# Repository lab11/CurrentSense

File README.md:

CurrentSense
============

CurrentSense is a tool for measuring current in embedded systems.

Usage
-----

Description of the inputs:

- **Power Supply**: 3.3-6 volts that supplies power to the measurement circuitry.
- **Optional Test Input**: This input can be used to power the load under test.
This is particularly useful for energy-harvesting or other systems where the input
power is not stable.
- **I_Sense**: The measurable output signal that is proportional to current.
To calculate current, divide the I_Sense signal (in volts) by the number
that corresponds to the selected range value. This will return the current
in amps.
- **Range**: Select the maximum current you want to measure. Select this as
close to the maximum you wish to measure as possible.
- **Load VCC Select**: This selects how you would like to power the load under
test. The options
  - Power Supply: Use the input from the power supply that is powering the
  measurement circuitry to also power the load.
  - 3V3: Use the onboard regulated 3.3 V rail to power the load.
  - Test Input: Use the external test input to power the load.
- **To Load**: Connect to VCC or the signal you wish to measure.
- **GND**: A set of ground pins for convenience.

Errata
------

The 300 mA range doesn't seem to work on v3.

----

V2 Notes
--------

You need a power selection jumper. You usually want to power the board externally,
in which case you'll want the jumper in the high position as pictured.

 - Connect external power (3.3-6V) to the EXT header at the top right.
   I usually also connect the external power to the GND header up here.
 - Connect the power supply for your target to VIN header.
 - Connect the VCC of your target to the VCC header
 - Connect the GND of your target to the GND header.
   I usually connect target GND to the GND header at the bottom, whose label is
   occluded by the screw.
 - Hook the scope probe to the test point at the top left (and GND anywhere)
 
The rest of the board is the same idea as above. Choose a range, measure voltage,
divide by the number on the board, get amperage.

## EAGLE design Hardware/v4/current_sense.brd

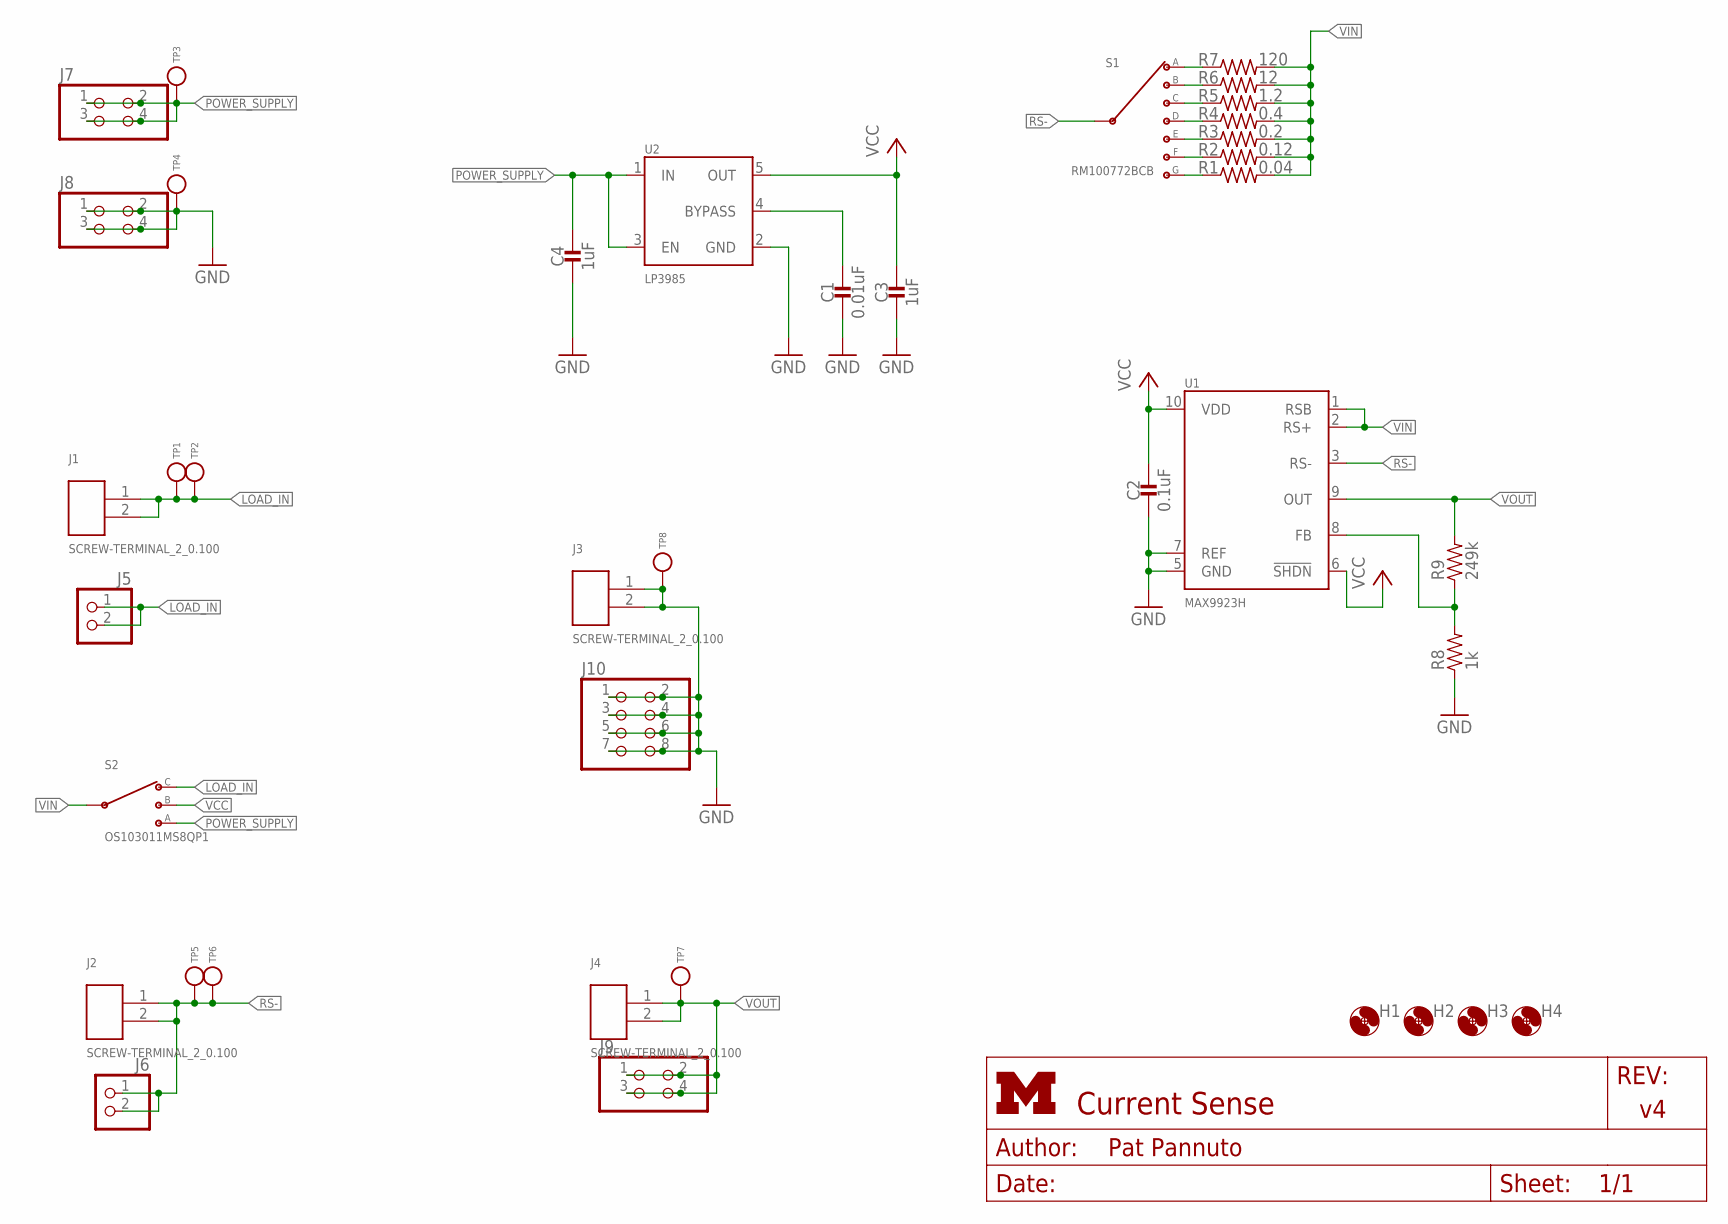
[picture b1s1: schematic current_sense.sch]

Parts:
C1: 0.01uF; 0603_CAP; MPN C1608X7R1E103K080AA; DIGIKEY 445-5100-1-ND
C2: 0.1uF; 0603_CAP; MPN C1608X7R1E104K080AA; DIGIKEY 445-1316-1-ND
C3, C4: 1uF; 0603_CAP; MPN C1608X7R1C105K080AC; DIGIKEY 445-1604-1-ND
H1, H2, H3, H4: MOUNT-HOLE3.2; 3,2
J1, J2, J3, J4: SCREW-TERMINAL_2_0.100; CONN_BLOCK_2
J5, J6: PINHD-1X2; 1X02
J7, J8, J9: PINHD-2X2; 2X02
J10: PINHD-2X4; 2X04
R1: 0.04; R1206; MPN RL1206FR-070R04L; DIGIKEY 311-.04LWCT-ND
R2: 0.12; R1206; MPN RL1632R-R120-F; DIGIKEY RL16R.12FCT-ND
R3: 0.2; R1206; MPN CSR1206FKR200; DIGIKEY CSR1206FKR200CT-ND
R4: 0.4; R1206; MPN RL1206FR-070R4L; DIGIKEY 311-.4LWCT-ND
R5: 1.2; R0805; MPN RL1220S-1R2-F; DIGIKEY RL12S1.2FCT-ND
R6: 12; R0805; MPN CPF0805B12RE1; DIGIKEY A103150CT-ND
R7: 120; R0805; MPN RG2012N-121-W-T1; DIGIKEY RG20N120WCT-ND
R8: 1k; 0603-RES; MPN ERA-3AEB102V; DIGIKEY P1.0KDBCT-ND
R9: 249k; 0603-RES; MPN ERA-3AEB2493V; DIGIKEY P249KDBCT-ND
S1: RM100772BCB; RM-SWITCH; MPN RM107772BCB; DIGIKEY CKN10705-ND
S2: OS103011MS8QP1; OS102011MS8QP1
TP1, TP2, TP3, TP4, TP5, TP6, TP7: TEST_POINT_0.040IN; TESTPOINT_0.040IN
TP8: TEST_POINT_0.112IN; TESTPOINT_0.112IN
U1: MAX9923H; UMAX10; MPN MAX9922EUB+T; DIGIKEY MAX9922EUB+TCT-ND
U2: LP3985; R-PDSO-G5

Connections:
GND: C1.2, C2.2, C3.2, C4.2, J3.1, J3.2, J8.1, J8.2, J8.3, J8.4, J10.1, J10.2, J10.3, J10.4, J10.5, J10.6, J10.7, J10.8, R8.1, TP4.TESTPOINT, TP8.1, U1.5 (GND), U1.7 (REF), U2.2 (GND)
LDO_BYPASS: C1.1, U2.4 (BYPASS)
LOAD_IN: J1.1, J1.2, J5.1, J5.2, S2.4 (3), TP1.TESTPOINT, TP2.TESTPOINT
POWER_SUPPLY: C4.1, J7.1, J7.2, J7.3, J7.4, S2.1, TP3.TESTPOINT, U2.1 (IN), U2.3 (EN)
RS-: J2.1, J2.2, J6.1, J6.2, S1.C (INPUT), TP5.TESTPOINT, TP6.TESTPOINT, U1.3 (RS-)
RS-_1MA: R6.1, S1.2 (B)
RS-_10MA: R5.1, S1.3 (C)
RS-_30MA: R4.1, S1.4 (D)
RS-_60MA: R3.1, S1.5 (E)
RS-_100MA: R2.1, S1.6 (F)
RS-_100UA: R7.1, S1.1 (A)
RS-_300MA: R1.1, S1.7 (G)
SENSE_FB: R8.2, R9.1, U1.8 (FB)
VCC: C2.1, C3.1, S2.3 (2), U1.6 (!SHDN), U1.10 (VDD), U2.5 (OUT)
VIN: R1.2, R2.2, R3.2, R4.2, R5.2, R6.2, R7.2, S2.2 (C), U1.1 (RSB), U1.2 (RS+)
VOUT: J4.1, J4.2, J9.1, J9.2, J9.3, J9.4, R9.2, TP7.TESTPOINT, U1.9 (OUT)

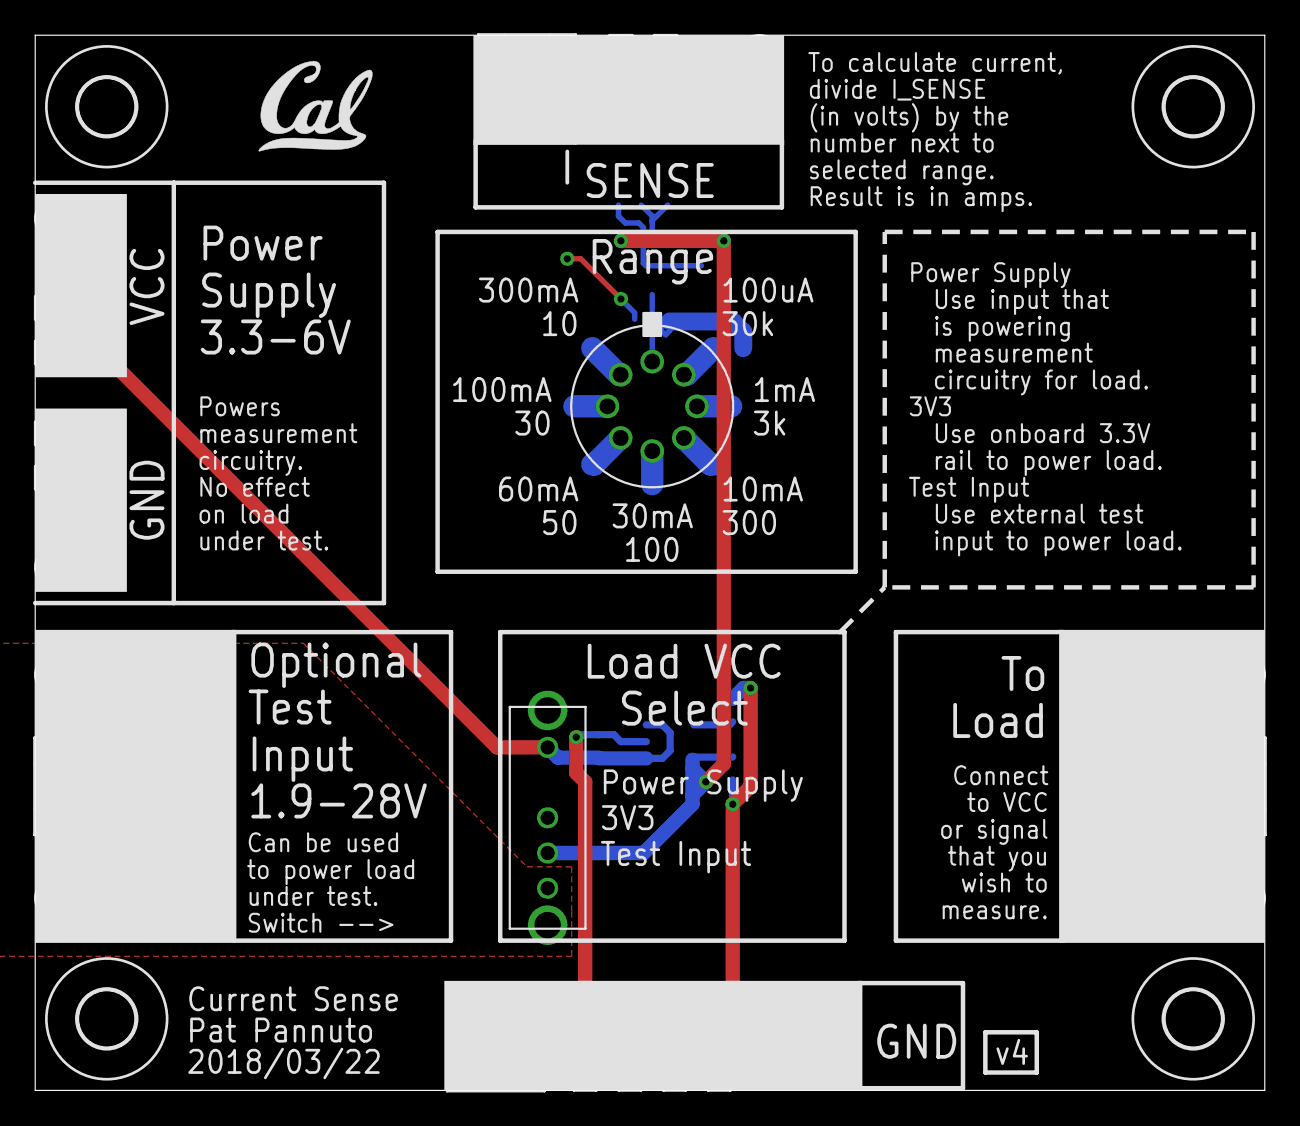
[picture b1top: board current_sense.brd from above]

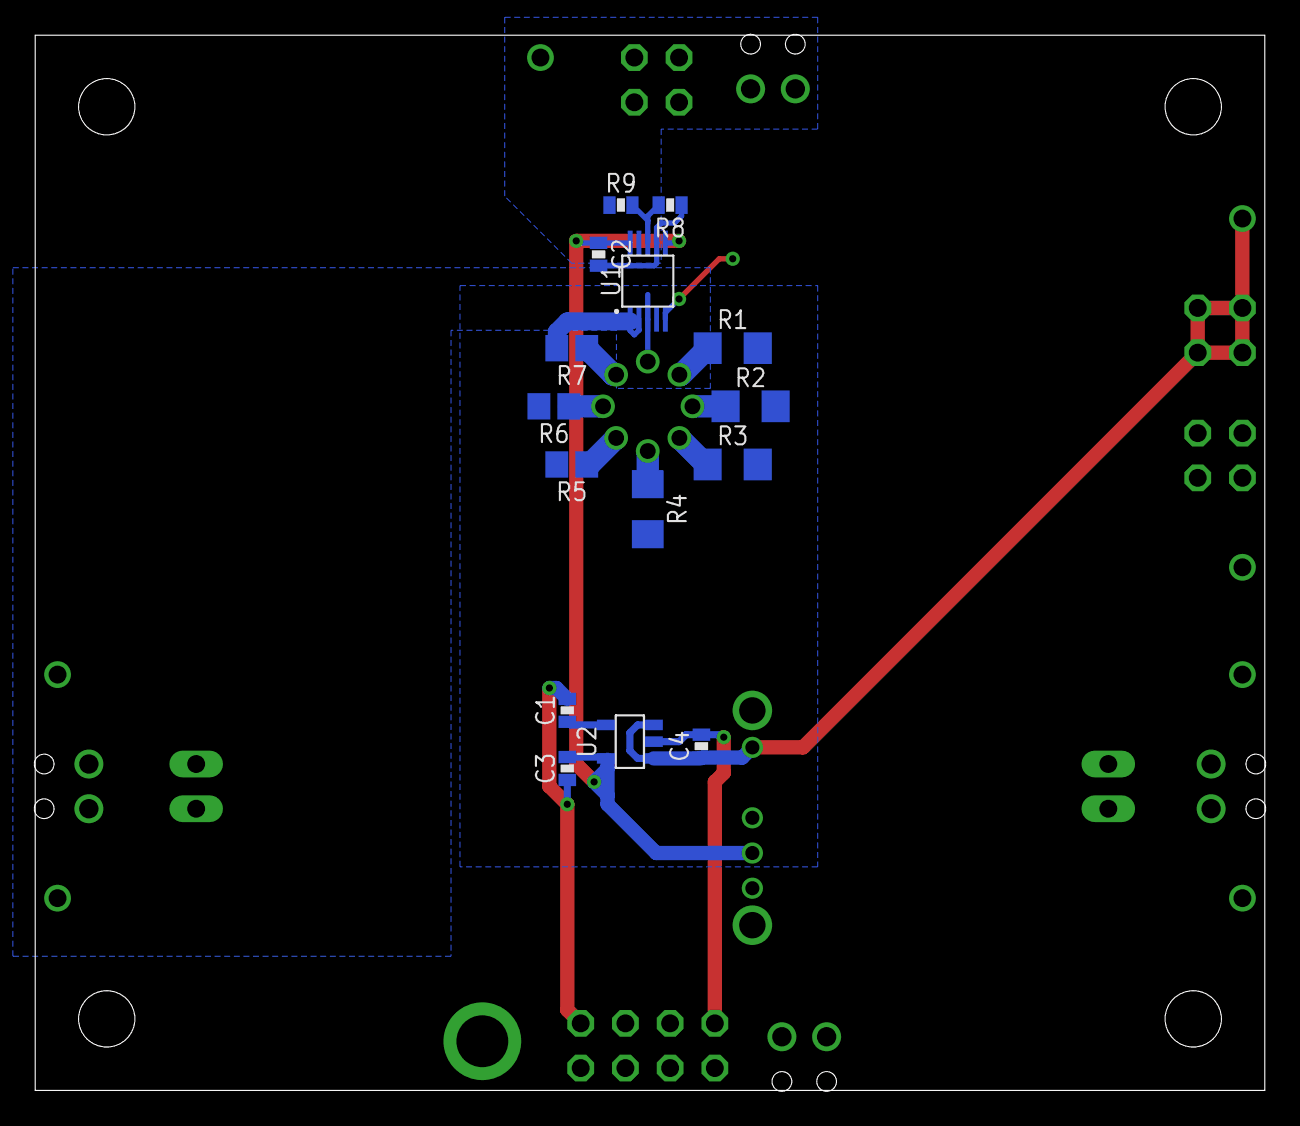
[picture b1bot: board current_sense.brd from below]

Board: 2 copper layers, 69.8 x 59.9 mm, 40 parts (15 on the bottom side), 16 nets.

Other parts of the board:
U$1: UCB_CAL_200MIL

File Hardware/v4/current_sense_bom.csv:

# Bill of Materials,,,,,,,,
# Converted from {},,,,,,,,
# Generated by bom_to_text.py,,,,,,,,
#,,,,,,,,
,,,,,,,,
Qty,Value,Device,Package,Parts,Description,DIGIKEY,MOUSER,NEWARK
1,0.01uF,CAPACITOR0603_CAP,0603_CAP,C1,0402 Capacitor,445-1304-1-ND,,
1,0.1uF,CAPACITOR0603_CAP,0603_CAP,C2,0402 Capacitor,445-1316-1-ND,,
2,1uF,CAPACITOR0603_CAP,0603_CAP,"C3, C4",0402 Capacitor,445-1604-1-ND,,
4,SCREW-TERMINAL_2_0.100,SCREW-TERMINAL_2_0.100,CONN_BLOCK_2,"J1, J2, J3, J4",2x 0.100 in screw terminal block,277-1273-ND,651-1725656,71C4107
2,,PINHD-1X2,1X02,"J5, J6",PIN HEADER,,,
3,,PINHD-2X2,2X02,"J7, J8, J9",PIN HEADER,,,
1,,PINHD-2X4,2X04,J10,PIN HEADER,,,
1,0.04,R-US_R1206,R1206,R1,"RESISTOR, American symbol",311-.04LWCT-ND,,
1,0.12,R-US_R1206,R1206,R2,"RESISTOR, American symbol",RL16R.12FCT-ND,,
1,0.2,R-US_R1206,R1206,R3,"RESISTOR, American symbol",CSR1206FKR200CT-ND,,
1,0.4,R-US_R1206,R1206,R4,"RESISTOR, American symbol",311-.4LWCT-ND,,
1,1.2,R-US_R0805,R0805,R5,"RESISTOR, American symbol",RL12S1.2FCT-ND,,
1,12,R-US_R0805,R0805,R6,"RESISTOR, American symbol",A103150CT-ND,,
1,120,R-US_R0805,R0805,R7,"RESISTOR, American symbol",RG20N120WCT-ND,,
1,1k,RESISTOR0603_RES,0603-RES,R8,Resistor,P1.0KDBCT-ND,,
1,249k,RESISTOR0603_RES,0603-RES,R9,Resistor,P249KDBCT-ND,,
1,RM107772BCB,RM107772BCB,RM-SWITCH,S1,Rotary Switch 8 Position SP7T 500mA (DC) 24VDC Through Hole,CKN10705-ND,,
1,OS103011MS8QP1,OS103011MS8QP1,OS102011MS8QP1,S2,Slide Switch SP3T Through Hole,CKN9543-ND,,
7,TEST_POINT_0.040IN,TEST_POINT_0.040IN,TESTPOINT_0.040IN,"TP1, TP2, TP3, TP4, TP5, TP6, TP7",0.040in Test Point,5001K-ND,,
1,TEST_POINT_0.112IN,TEST_POINT_0.112IN,TESTPOINT_0.112IN,TP8,"Solder terminal, turreted",,,40F6015
1,MAX9922,MAX9922,UMAX10,U1,"The MAX9922/MAX9923 ultra-precision, high-side current-",MAX9922EUB+TCT-ND ,,
1,LP3985,LP3985,R-PDSO-G5,U2,Linear Voltage Regulator IC Positive Fixed 1 Output 3.3V 150mA SOT-23-5,LP3985IM5-3.3/NOPBCT-ND,,

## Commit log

2015-02-07 altium files
2015-02-07 basic readme
2015-06-30 add v2 hardware
2016-11-09 start on rev 3
2016-11-09 better silkscreen
2016-11-09 renumbered parts and added bom
2016-11-11 updated current sense and zips
2016-12-17 fix html
2018-02-09 Add pic of v2 board
2018-02-09 Add some directions for the v2 board
    Because I always forget
2018-03-22 add v4 (copy of v3)
2018-03-22 Fix resistance issues, all doc on silk now
2018-03-22 update global attrs
2018-03-23 v4: fatten more traces because why not
2018-03-23 v4: update attrs
2018-03-23 v4: add hardware files
2018-03-23 ignore hw artifacts
